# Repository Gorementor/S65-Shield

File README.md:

# S65-Shield
The S65-Shield is a plug-on module with color TFT-Display (176x132), microSD socket and rotary encoder for Arduino/Genuino.

## Features
* Color-Display (176x132)
* Rotary-Encoder
* microSD Socket (SPI)

## Hardware
* 
* [Schematics + Layout](https://github.com/watterott/S65-Shield/tree/master/hardware)

## Software
* [Arduino Library and Examples](https://github.com/watterott/Arduino-Libs)
* [Old Arduino Library and Examples](https://github.com/watterott/S65-Shield/tree/da4eeeb2683e48dbeafd6923b010ca1eb41107df/src)

## Projects
* Misc Arduino Programs: http://www.mon-club-elec.fr/pmwiki_mon_club_elec/pmwiki.php?n=MAIN.ArduinoExpertTFTGraphCouleur
* Monitor for Nagios + Icinga: http://blog.makezine.com/2009/05/11/naguino-an-arduino-based-lcd-monito/
* Arduino Pong: http://www.codetorment.com/2009/11/11/arduino-pong-using-s65-shield/
* PONGuino: http://lab.synoptx.net/2010/02/12/ponguino-arduino-s65-shield-2-player-minigame/
* SMSlingshot: http://www.vrurban.org/smslingshot.html
* Different projects (French): http://www.mon-club-elec.fr/pmwiki_mon_club_elec/pmwiki.php?n=Category.TFT
* R2D2 Robot: http://www.youtube.com/watch?v=hYIbPEHO2PI http://www.youtube.com/watch?v=OyuvxOONDeE
* TinyCLR/FEZ + S65-Shield: http://robotics-visionexperiments.blogspot.de/2011/02/watterott-s65-shield-with-fez-domino.html

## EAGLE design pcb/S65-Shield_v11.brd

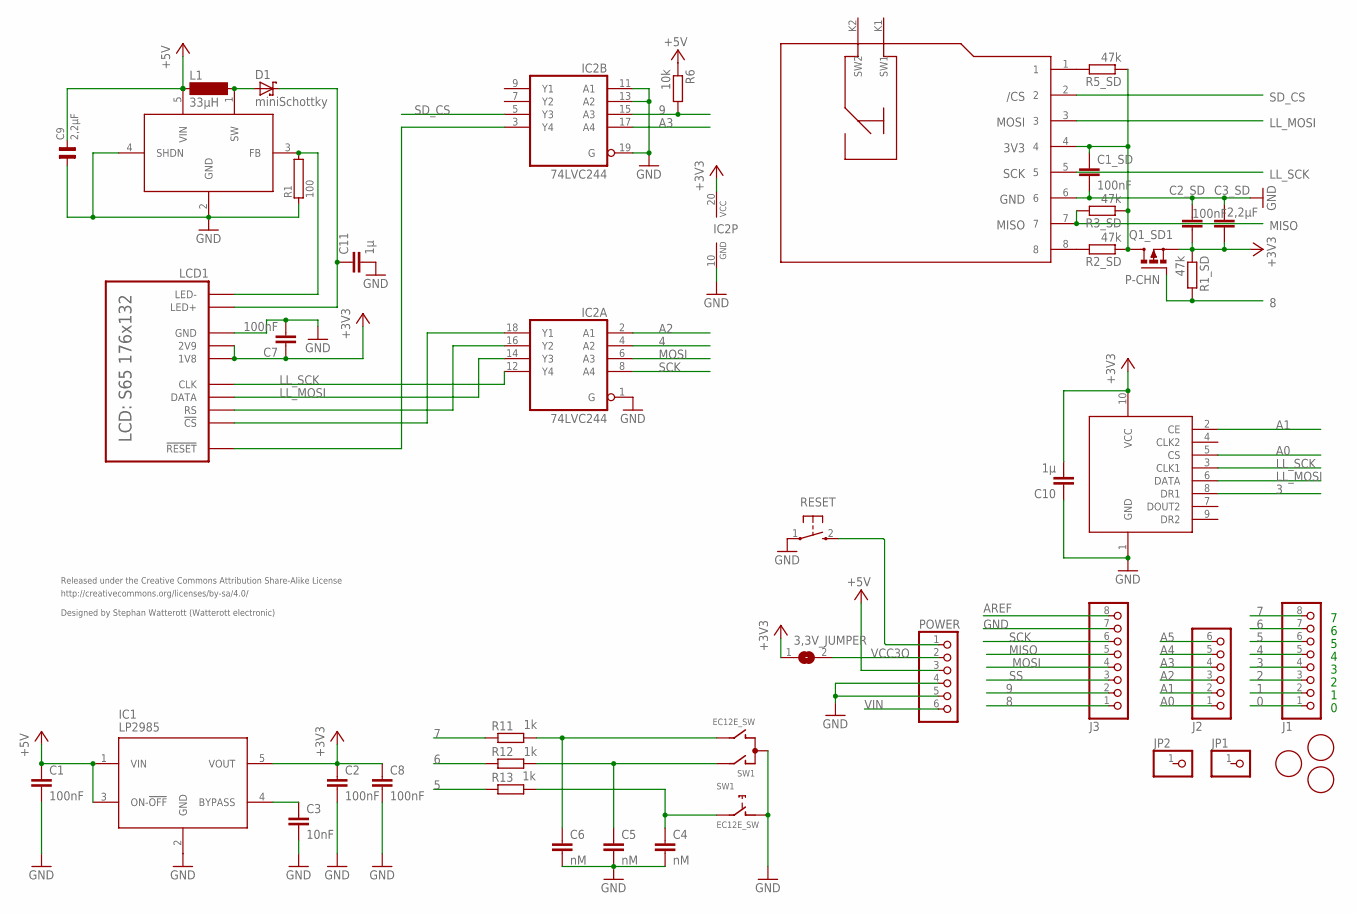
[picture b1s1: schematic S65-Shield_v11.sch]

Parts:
3,3V_JUMPER: SJ
C1, C1_SD, C2, C2_SD, C7: 100nF; C0603
C3: 10nF; C0603
C3_SD: 2,2µF; C0805
C4, C5, C6: nM; C0603
C8: 100nF; C0805
C9: 2,2µF; 0805
C10, C11: 1µ; C0603
D1: miniSchottky; D0603
IC1: LP2985; SOT23-5
IC2: 74LVC244; SO20W
J1, J3: PINHD-1X8; 1X08
J2: PINHD-1X6; 1X06
JP1, JP2: PINHD-1X1; 1X01
L1: 33µH; MS42
LCD1: S65
POWER: PINHD-1X6; 1X06
Q1_SD1: P-CHN; MICRO3
R1: 100; 0603
R1_SD, R2_SD, R3_SD, R5_SD: 47k; R0603
R6: 10k; R0603
R11, R12, R13: 1k; R0603
RESET: TAST_SMD1; SMD_TASTER
SD: MICRO-SD
SW1: EC12E_SW; ALPS_EC12E_SW
U$1, U$2, U$3: FIDUCIALMOUNT; FIDUCIA-MOUNT
U$4: LM2705; SOT23-5
U$5: TRW-2.4G

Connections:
0: J1.1
1: J1.2
2: J1.3
3: J1.4, U$5.8 (DR1)
4: IC2.4 (A2), J1.5
5: J1.6, R13.1
6: J1.7, R12.1
7: J1.8, R11.1
8: J3.1, Q1_SD1.1 (G), R1_SD.2
9: IC2.15 (A3), J3.2, R6.2
+3V3: 3,3V_JUMPER.1, C2.1, C2_SD.2, C3_SD.2, C7.1, C8.1, C10.2, IC1.5 (VOUT), IC2.20 (VCC), LCD1.1V8, LCD1.2V9, Q1_SD1.2 (S), R1_SD.1, U$5.10 (VCC)
+5V: C1.1, C9.2, IC1.1 (VIN), IC1.3 (ON-!OFF), L1.1, POWER.3, R6.1, U$4.5 (VIN)
A0: J2.1, U$5.5 (CS)
A1: J2.2, U$5.2 (CE)
A2: IC2.2 (A1), J2.3
A3: IC2.17 (A4), J2.4
A4: J2.5
A5: J2.6
AREF: J3.8
GND: C1.2, C1_SD.2, C2.2, C2_SD.1, C3.2, C3_SD.1, C4.2, C5.2, C6.2, C7.2, C8.2, C9.1, C10.1, C11.2, IC1.2 (GND), IC2.1 (G), IC2.10 (GND), IC2.11 (A1), IC2.13 (A2), IC2.19 (G), J3.7, LCD1.GND, POWER.4, POWER.5, R1.1, RESET.1, SD.6, SW1.C, SW1.D (1), U$4.2 (GND), U$4.4 (SHDN), U$5.1 (GND)
LED+: C11.1, D1.1 (C), LCD1.LED+
LED-: LCD1.LED-, R1.2, U$4.3 (FB)
LL_MOSI: IC2.14 (Y3), LCD1.DATA, SD.3, U$5.6 (DATA)
LL_SCK: IC2.12 (Y4), LCD1.CLK, SD.5, U$5.3 (CLK1)
MISO: J3.5, R3_SD.2, SD.7
MOSI: IC2.6 (A3), J3.4
unnamed: R5_SD.2, SD.1
unnamed: IC2.16 (Y2), LCD1.RS
unnamed: IC2.18 (Y1), LCD1.CS (!CS)
unnamed: IC2.3 (Y4), LCD1.RESET (!RESET)
unnamed: D1.2 (A), L1.2, U$4.1 (SW)
unnamed: C4.1, R13.2, SW1.E (2)
unnamed: C5.1, R12.2, SW1.A
unnamed: C6.1, R11.2, SW1.B
unnamed: C3.1, IC1.4 (BYPASS)
unnamed: POWER.1, RESET.2 (S)
unnamed: R2_SD.2, SD.8
SCK: IC2.8 (A4), J3.6
SD_3V3: C1_SD.1, Q1_SD1.3 (D), R2_SD.1, R3_SD.1, R5_SD.1, SD.4
SD_CS: IC2.5 (Y3), SD.2
SS: J3.3
VCC3O: 3,3V_JUMPER.2, POWER.2
VIN: POWER.6

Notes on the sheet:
Released under the Creative Commons Attribution Share-Alike License
http://creativecommons.org/licenses/by-sa/4.0/
Designed by Stephan Watterott (Watterott electronic)

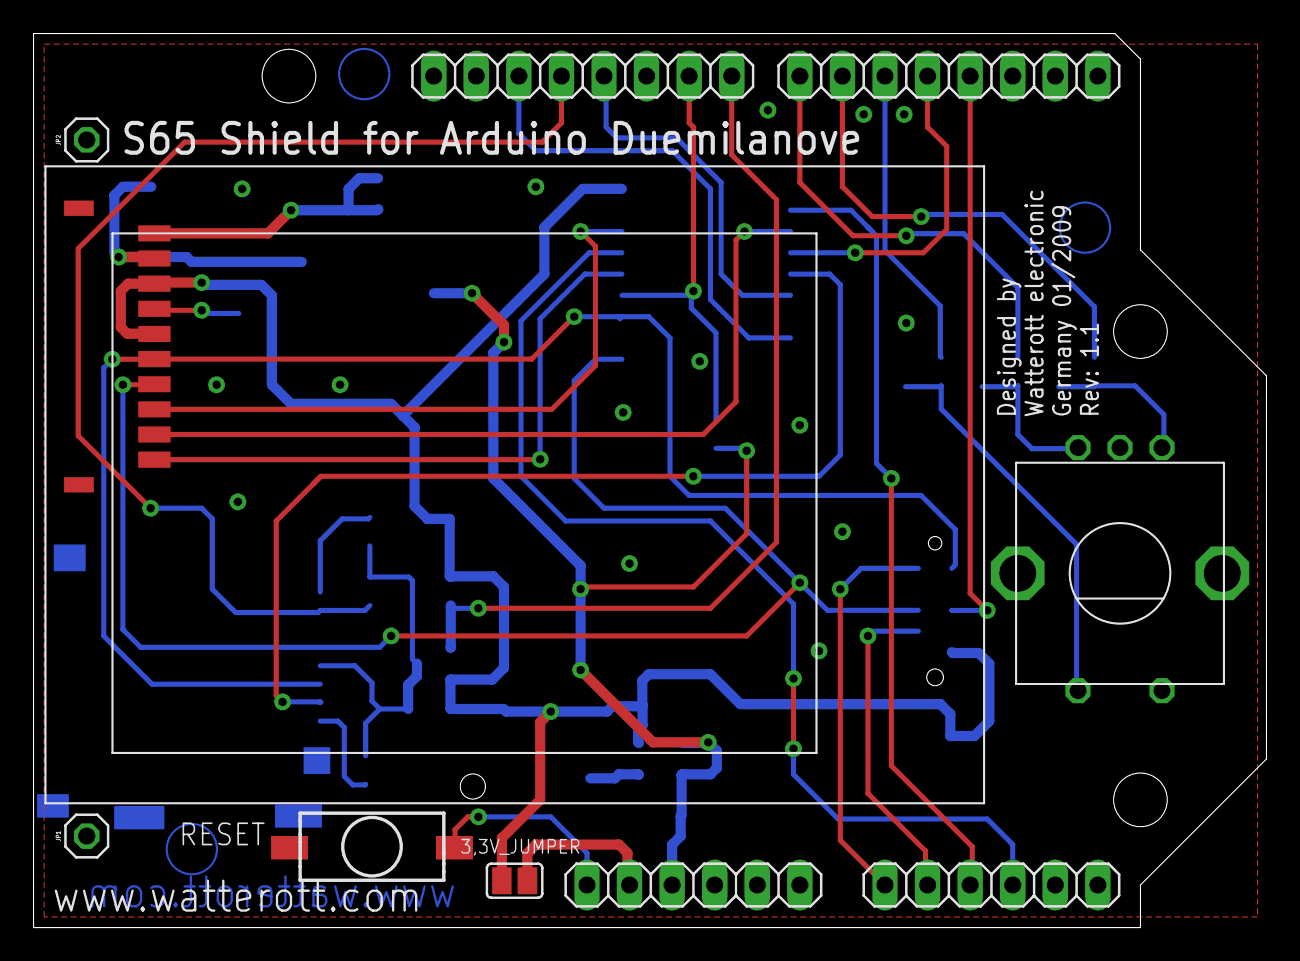
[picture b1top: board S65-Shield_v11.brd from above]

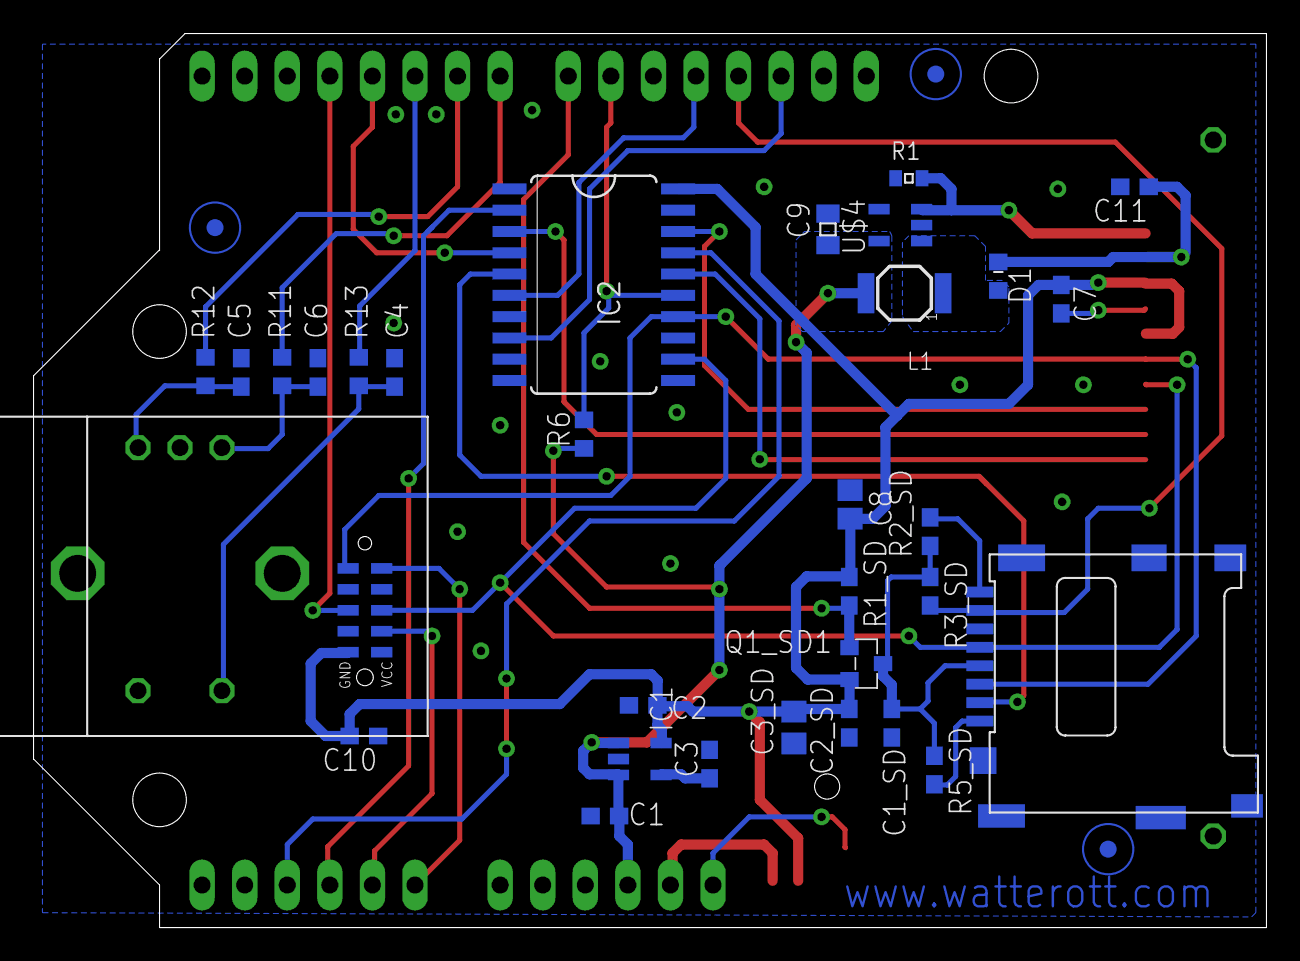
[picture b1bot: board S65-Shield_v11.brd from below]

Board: 2 copper layers, 73.6 x 53.3 mm, 44 parts (34 on the bottom side), 35 nets.

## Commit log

2012-03-11 Lib V0.22 added schematics and layout files
2012-03-11 added license information
2012-03-27 Support for Arduino 1.0 S65Display Mega bugfix
2012-03-27 updated to FatFs 0.08b
2012-03-28 readme updated
2012-05-31 new directory struct
2013-03-11 added project list
2013-05-20 changed docu format
2013-05-27 updated docu
2013-07-31 minor changes
2013-09-21 updated hardware diagram
2013-10-01 Lib v0.24
2013-10-09 updated readme and docu
2014-04-19 updated schematics and layout files
2014-04-19 moved Arduino lib
2014-11-06 cleaned up schematics and layout
2015-01-11 moved image
2015-08-21 changed path structure
